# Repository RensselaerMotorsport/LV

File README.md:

# LV
Repo for all LV Hardware Design

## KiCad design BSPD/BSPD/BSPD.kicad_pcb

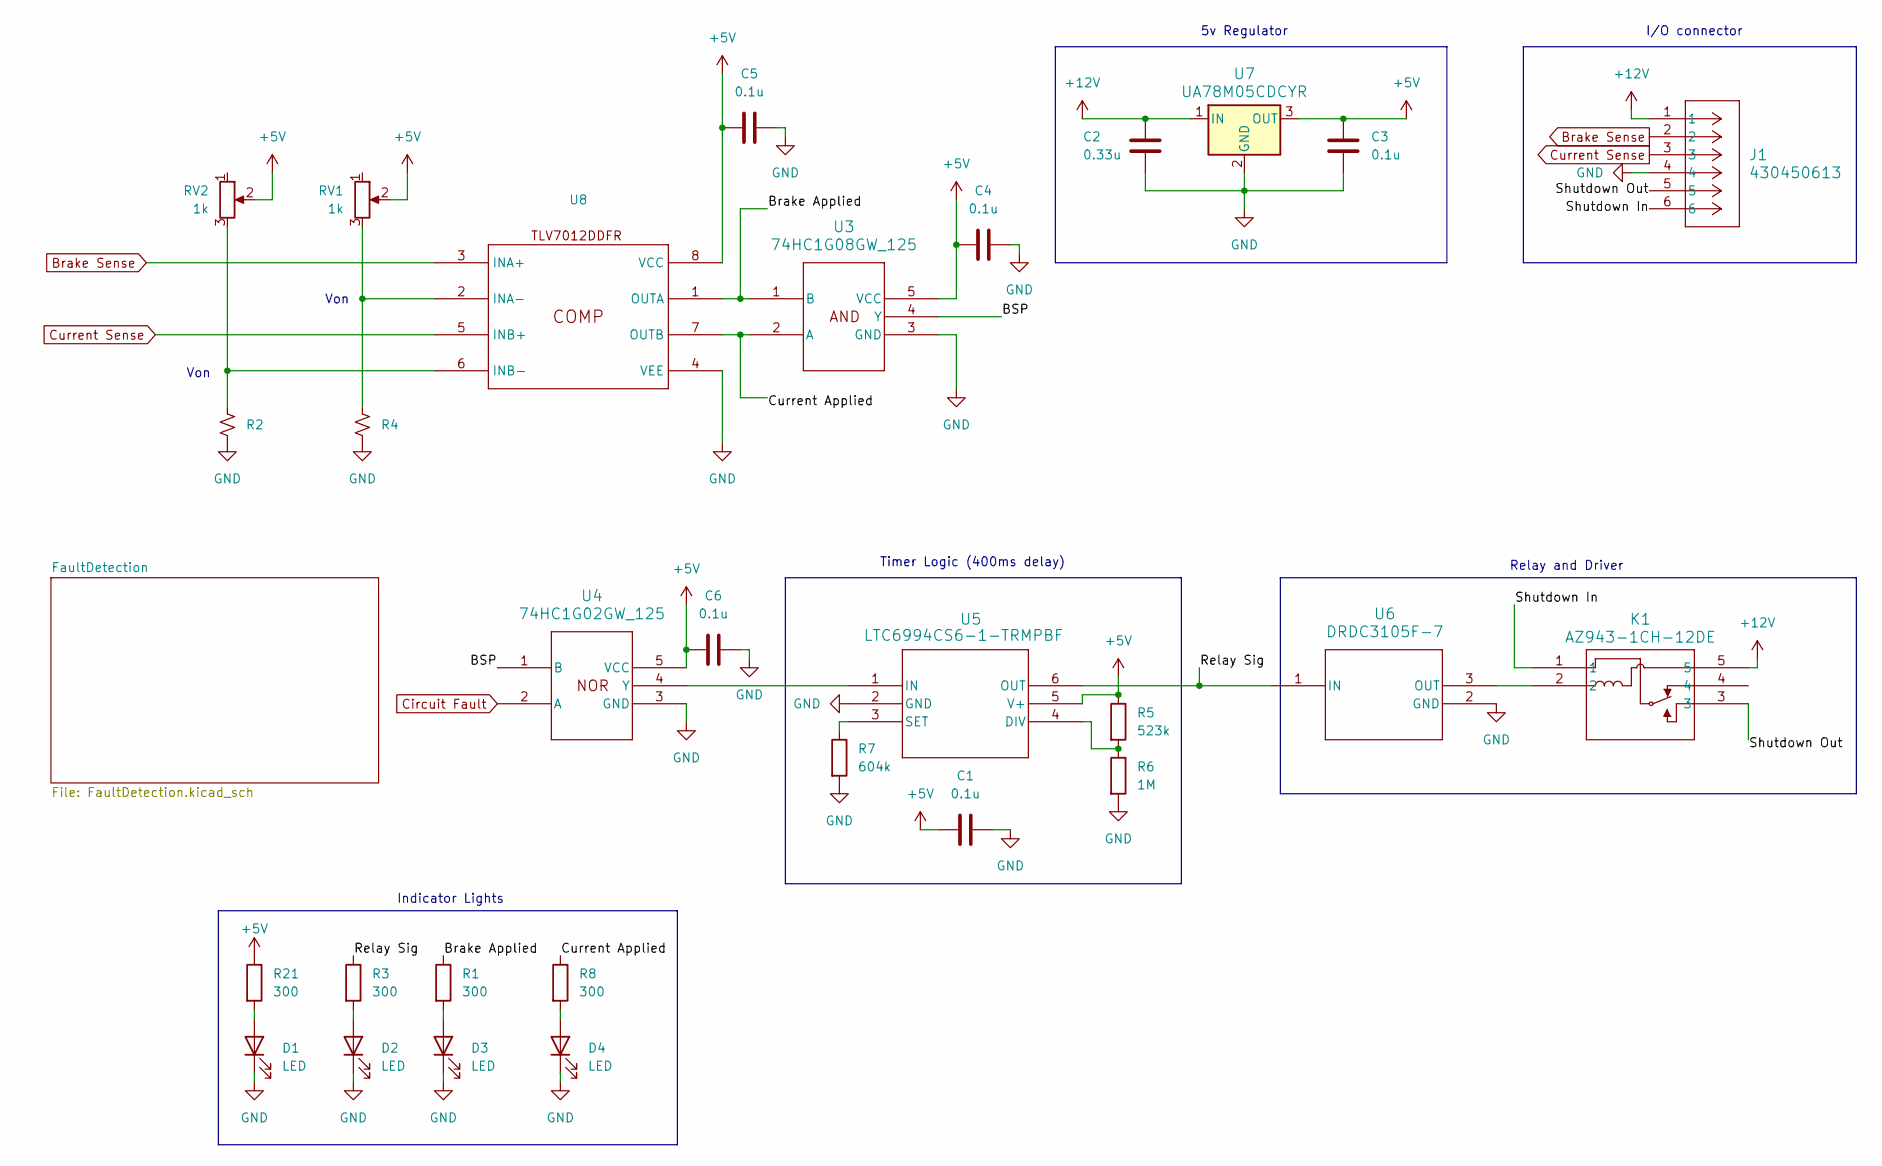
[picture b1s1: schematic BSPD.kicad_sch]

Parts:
C1, C3, C4, C5, C6: 0.1u; CAP_CL10_SAM
C2: 0.33u; CAP_CL10_SAM
D1, D2, D3, D4: LED; LED0805N_CML
J1: 430450613; CONN_SD-43045-005_06_MOL
K1: AZ943-1CH-12DE; AZ943-1CH_AMZ
R1, R3, R8, R21: 300; R_0603_1608Metric_Pad0.98x0.95mm_HandSolder
R2, R4: R_Small_US; R_0603_1608Metric_Pad0.98x0.95mm_HandSolder
R5: 523k; R_0603_1608Metric_Pad0.98x0.95mm_HandSolder
R6: 1M; R_0603_1608Metric_Pad0.98x0.95mm_HandSolder
R7: 604k; R_0603_1608Metric_Pad0.98x0.95mm_HandSolder
RV1, RV2: 1k; RES3_PV36W103C01B00_BRN
U3: 74HC1G08GW_125; SOT-353_SC-70-5
U4: 74HC1G02GW_125; SOT-353_SC-70-5
U5: LTC6994CS6-1-TRMPBF; TSOT-23_S6_LIT
U6: DRDC3105F-7; SOT23_DIO
U7: UA78M05CDCYR; SOT-223-3_TabPin2
U8: SOT-23-8

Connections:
+5V: C1.1, C3.1, C4.1, C5.1, C6.1, R5.1, R21.1, RV1.2, RV2.2, U3.5 (VCC), U4.5 (VCC), U5.5 (V+), U7.3 (OUT), U8.8 (VCC); also elsewhere on the board
+12V: C2.1, J1.1, K1.5, U7.1 (IN)
/BSP: U3.4 (Y), U4.1 (B)
/Brake Applied: R1.1, U3.1 (B), U8.1 (OUTA)
/Current Applied: R8.1, U3.2 (A), U8.7 (OUTB)
/Relay Sig: R3.1, U5.6 (OUT), U6.1 (IN)
/Shutdown In: J1.6, K1.1
/Shutdown Out: J1.5, K1.3
Brake Sense: J1.2, U8.3 (INA+); also elsewhere on the board
Circuit Fault: U4.2 (A); also elsewhere on the board
Current Sense: J1.3, U8.5 (INB+); also elsewhere on the board
GND: C1.2, C2.2, C3.2, C4.2, C5.2, C6.2, D1.1 (K), D2.1 (K), D3.1 (K), D4.1 (K), J1.4, R2.2, R4.2, R6.2, R7.2, U3.3 (GND), U4.3 (GND), U5.2 (GND), U6.2 (GND), U7.2 (GND), U8.4 (VEE); also elsewhere on the board
unnamed: D1.2 (A), R21.2
unnamed: D2.2 (A), R3.2
unnamed: D3.2 (A), R1.2
unnamed: D4.2 (A), R8.2
unnamed: U4.4 (Y), U5.1 (IN)
unnamed: R5.2, R6.1, U5.4 (DIV)
unnamed: R7.1, U5.3 (SET)
unnamed: K1.2, U6.3 (OUT)
unnamed: R4.1, RV1.3, U8.2 (INA-)
unnamed: R2.1, RV2.3, U8.6 (INB-)

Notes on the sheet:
Von
Relay and Driver
5v Regulator
I/O connector
Indicator Lights
Timer Logic (400ms delay)

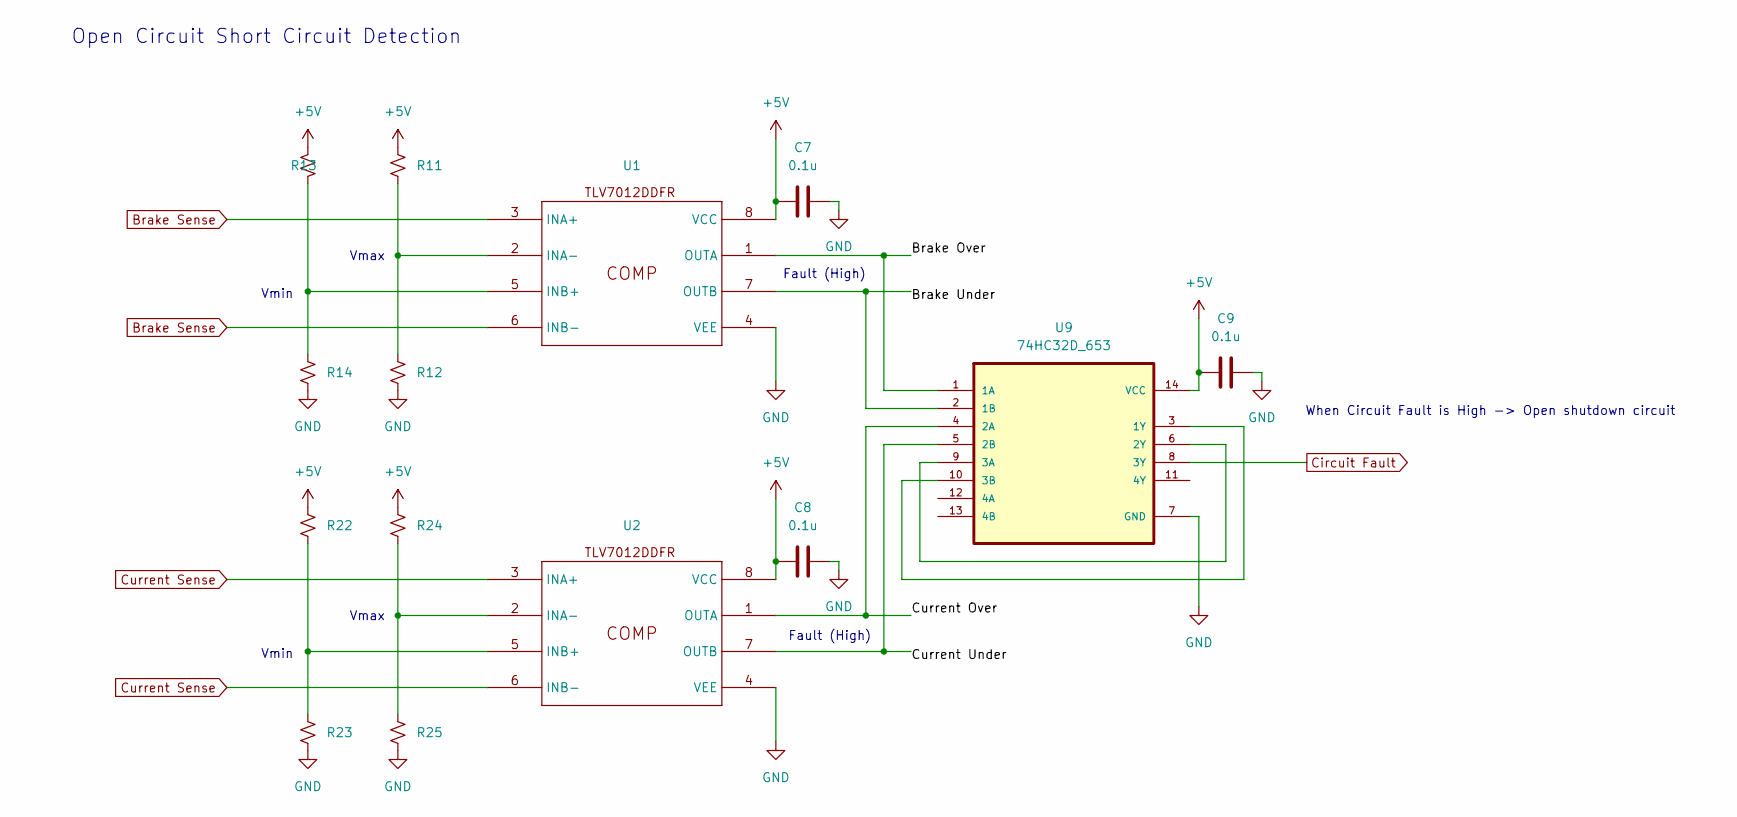
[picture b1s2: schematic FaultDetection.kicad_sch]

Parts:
C7, C8, C9: 0.1u; CAP_CL10_SAM
R11, R12, R13, R14, R22, R23, R24, R25: R_Small_US; R_0603_1608Metric_Pad0.98x0.95mm_HandSolder
U1, U2: SOT-23-8
U9: 74HC32D_653; SO-14_5.3x10.2mm_P1.27mm; MPN 74HC32D,653

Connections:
+5V: C7.1, C8.1, C9.1, R11.1, R13.1, R22.1, R24.1, U1.8 (VCC), U2.8 (VCC), U9.14 (VCC); also elsewhere on the board
/FaultDetection/Brake Over: U1.1 (OUTA), U9.1 (1A)
/FaultDetection/Brake Under: U1.7 (OUTB), U9.2 (1B)
/FaultDetection/Current Over: U2.1 (OUTA), U9.4 (2A)
/FaultDetection/Current Under: U2.7 (OUTB), U9.5 (2B)
Brake Sense: U1.3 (INA+), U1.6 (INB-); also elsewhere on the board
Circuit Fault: U9.8 (3Y); also elsewhere on the board
Current Sense: U2.3 (INA+), U2.6 (INB-); also elsewhere on the board
GND: C7.2, C8.2, C9.2, R12.2, R14.2, R23.2, R25.2, U1.4 (VEE), U2.4 (VEE), U9.7 (GND); also elsewhere on the board
unnamed: R11.2, R12.1, U1.2 (INA-)
unnamed: R13.2, R14.1, U1.5 (INB+)
unnamed: R24.2, R25.1, U2.2 (INA-)
unnamed: R22.2, R23.1, U2.5 (INB+)
unnamed: U9.3 (1Y), U9.10 (3B)
unnamed: U9.6 (2Y), U9.9 (3A)

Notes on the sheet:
Vmax
Fault (High)
Vmin
Open Circuit Short Circuit Detection
When Circuit Fault is High -> Open shutdown circuit

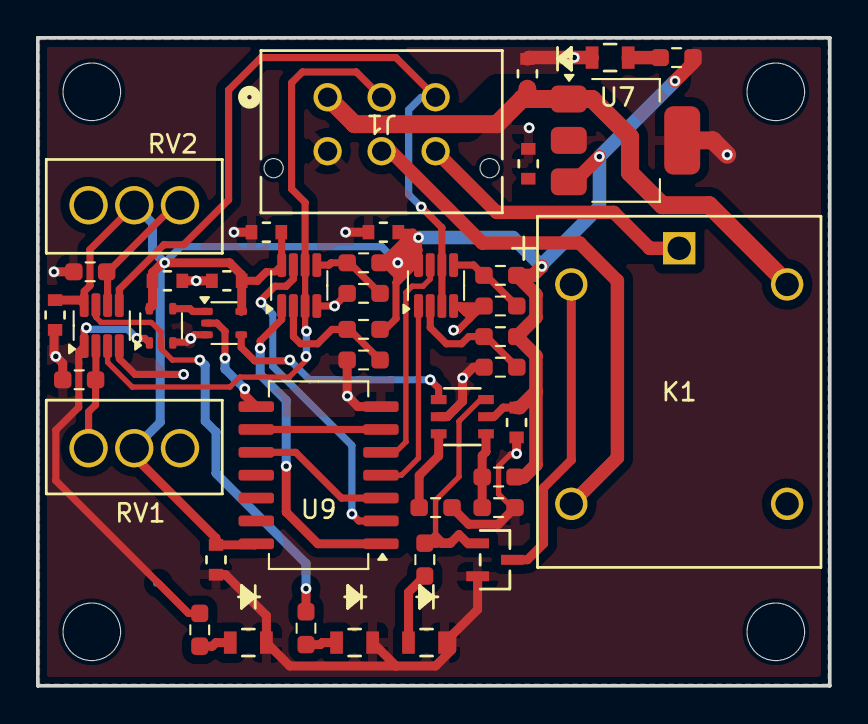
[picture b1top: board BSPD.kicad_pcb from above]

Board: 2 copper layers, 44.0 x 36.0 mm, 43 parts (0 on the bottom side), 32 nets.

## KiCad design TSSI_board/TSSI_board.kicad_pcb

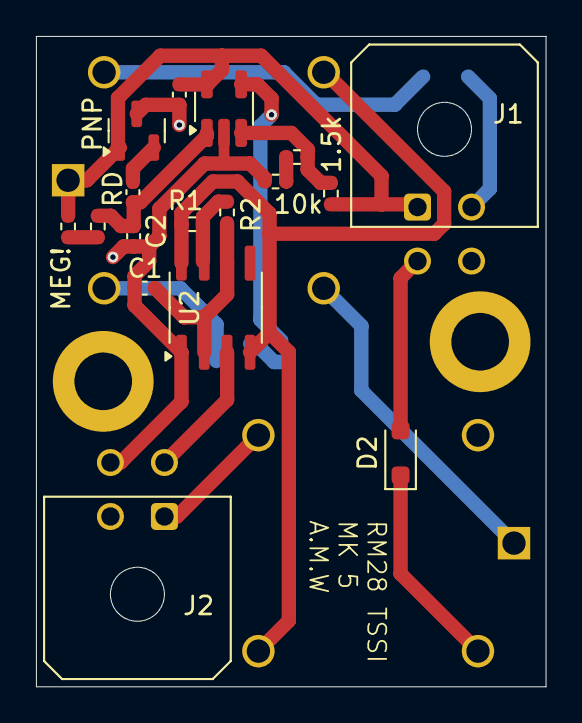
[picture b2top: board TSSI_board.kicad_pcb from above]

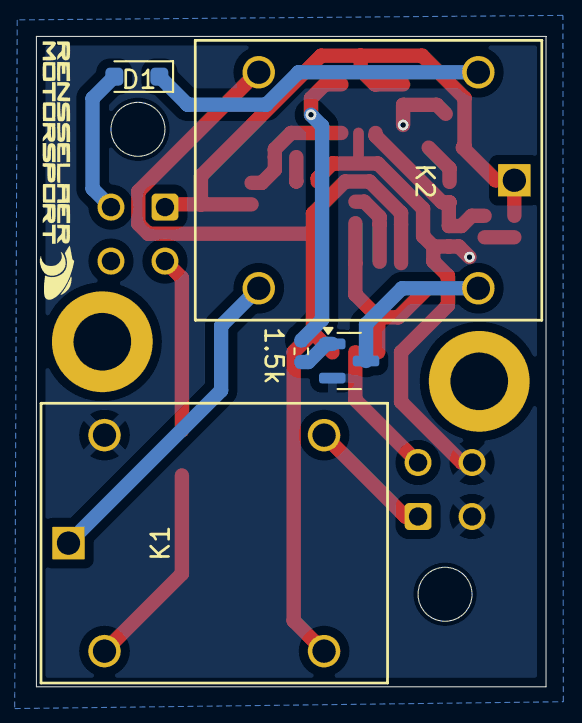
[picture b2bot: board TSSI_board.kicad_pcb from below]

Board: 2 copper layers, 28.3 x 36.1 mm, 18 parts (4 on the bottom side), 15 nets.

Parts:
1.5k, 1.5k#2, 10k: R_0402_1005Metric_Pad0.72x0.64mm_HandSolder
C1, C1#2: .47u; C_0402_1005Metric_Pad0.74x0.62mm_HandSolder
D1, D2: D; D_SOD-323_HandSoldering
J1, J2: Conn_01x04_Pin; Molex_Micro-Fit_3.0_43045-0400_2x02_P3.00mm_Horizontal
K1, K2: SANYOU_SRD_Form_C; K_AZ943-1C_AMZ
MEG!: R; R_0402_1005Metric_Pad0.72x0.64mm_HandSolder
PNP: PNP; SOT-23
R1: 15k; R_0402_1005Metric_Pad0.72x0.64mm_HandSolder
R2: 470k; R_0402_1005Metric_Pad0.72x0.64mm_HandSolder
R6: R; R_0402_1005Metric_Pad0.72x0.64mm_HandSolder
RD: R; C_0402_1005Metric_Pad0.74x0.62mm_HandSolder
U2: NE555D; SOIC-8_3.9x4.9mm_P1.27mm

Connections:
+12V: 1.5k.1, J1.1, K2.1, MEG!.2, PNP.1 (C)
BMS: D2.2 (A), J1.3
GND: 10k.2, C1.2, C1#2.2, J2.2, J2.4, K1.5, PNP.3 (E), U2.1 (GND)
IMD: D1.2 (A), J1.2
unnamed: D1.1 (K), K2.2
unnamed: D2.1 (K), K1.2
unnamed: J2.1, K1.4
unnamed: J2.3, U2.3 (Q)
unnamed: K1.1, K2.4
unnamed: PNP.2 (B), RD.1
unnamed: MEG!.1, R6.1
unnamed: R1.2, R2.2, U2.7 (DIS)
unnamed: K1.3, K2.3, R1.1, U2.4 (R), U2.8 (VCC)
unnamed: C1.1, R2.1, U2.2 (TR), U2.6 (THR)
unnamed: C1#2.1, R6.2, RD.2

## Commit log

2024-12-15 Started Diagrams for LV System Architecture
2024-12-15 Folder
2024-12-15 Communication Diagram Added
2024-12-15 Added old low level diagram for reference
2024-12-16 Addition and Improvement on Diagrams
2024-12-16 Added Diagram for Peripheral Placement
2025-03-23 BSPD Project File
2025-03-23 Started BSPD Schematic
2025-03-23 Timer and relay added/updated
    Added timer circuit and 12v relay that we used from shutdown pcb
2025-03-24 Relay Driver/Regulator/IO/LEDS/Comparator
    Added relay driver, 5v regulator, debugging leds, 6 pin microfit connector for IO, and created footprint for TLV7012DDFR comparator we're using
2025-03-24 Added logic gate symbols
2025-03-24 Added decoupling caps
2025-03-24 Configure Falling Edge Delay
    Swapped resistors on delay ic to detect a falling edge to align with other logic in circuit.
2025-03-26 Configured footprints and set board outline.
    All footprints have been assigned to the components, and the board size and it's mounting holes have been set up in the pcb editor.
2025-04-01 Layout started and component changes
    The footprints have all be chosen and the linear regulator was swapped out.
2025-04-01 Removed Lock file
    You're welcome Blake
2025-08-28 VCU Development
